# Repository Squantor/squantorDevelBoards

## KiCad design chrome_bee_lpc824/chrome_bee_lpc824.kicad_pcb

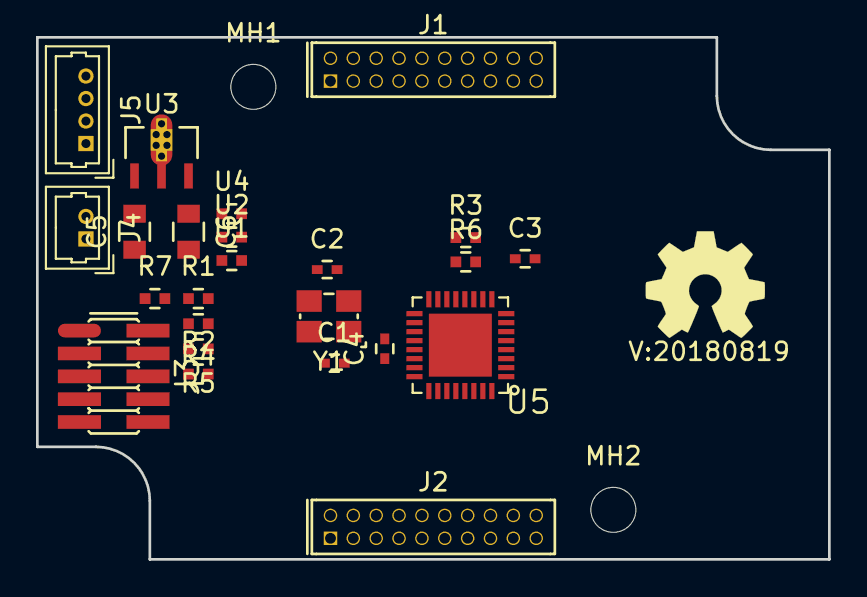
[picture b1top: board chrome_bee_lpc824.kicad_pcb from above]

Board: 4 copper layers, 44.0 x 29.0 mm, 28 parts (0 on the bottom side), 39 nets, no tracks yet.

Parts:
C1, C2: 10p; C_0402
C3, C4: 100n; C_0402
C5: 1mu; C_0805
C6: 10mu; C_0805
J1: DevBoardDigital; Header-0127-2X10-H006
J2: DevBoardAnalog; Header-0127-2X10-H006
J3: JTAG_2X05; Header-0127-2X05-SMD
J4: POWER_IN; Molex_PicoBlade_53047-0210_02x1.25mm_Straight
J5: BMP_UART; Molex_PicoBlade_53047-0410_04x1.25mm_Straight
MH1, MH2: MountingHole; MountingHole_2.5mm_no_metal
N1: OHWLOGO; OSHW-Symbol_6.7x6mm_SilkScreen
N2: 20180819; Label_version
R1, R2, R3: 100k; R_0402_hand
R4, R5, R6: 100; R_0402_hand
R7: 10; R_0402_hand
U1, U2, U4: POWER_JOINER; R_0402_hand
U3: MCP1702-MB; SOT89-ViaTab-Microchip-MB
U5: LPC824M201JHI33; SOT617-3
Y1: 12MHz; Crystal_3225_4

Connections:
/ANALOG0: J2.11, U5.22
/ANALOG1: J2.12, U5.23
/ANALOG2: J2.13, U5.25
/ANALOG3: J2.14, U5.26
/ANALOG4: J2.15, U5.27
/ANALOG5: J2.16, U5.28
/ANALOG6: J2.17, U5.29
/ANALOG7: J2.18, U5.30
/ANALOG8: J2.19, U5.31
/ANALOG9: J2.20, U5.32
/IO00_SDA: J1.5, U5.8
/IO01_SCL: J1.6, U5.9
/IO02_MOSI: J1.7, U5.2
/IO03_MISO: J1.8, U5.1
/IO04_SCK: J1.9, U5.15
/IO05_RXI: J1.10, J5.2, U5.10
/IO06_TXO: J1.11, J5.3, U5.14
/IO07: J1.12, U5.13
/IO08: J1.13, U5.12
/IO09: J1.14, U5.11
/IO10: J1.15, U5.5
/IO11: J1.16, U5.24
/IO12: J1.17, U5.16
/IO13: J1.18, U5.4
/RESET: R3.2, R6.1, U5.3
/SWDCLK: R2.2, R5.1, U5.6
/SWDIO: R1.2, R4.1, U5.7
/XTAL_IN: C1.1, U5.18, Y1.1
/XTAL_OUT: C2.1, U5.17, Y1.3
GND: C5.2, C6.2, J4.2, U1.1, U2.1, U3.1
unnamed: J3.1, R7.1
unnamed: J3.2, R4.2
unnamed: J3.4, R5.2
unnamed: J3.10, R6.2
VCC: C5.1, J2.1, J2.2, J4.1, J5.1, U3.2, U3.TAB
VDD: C3.1, C6.1, J1.1, J1.2, R1.1, R3.1, R7.2, U3.3, U4.1, U5.19
VDDA: C4.1, J2.5, J2.6, U4.2, U5.21
VSS: C1.2, C2.2, C3.2, J1.3, J1.4, J2.3, J2.4, J3.3, J3.5, J3.9, J5.4, R2.1, U1.2, U5.33, Y1.2, Y1.4
VSSA: C4.2, J2.7, J2.8, U2.2, U5.20

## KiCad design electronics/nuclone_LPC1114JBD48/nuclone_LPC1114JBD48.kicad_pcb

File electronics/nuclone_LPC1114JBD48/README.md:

# Nuclone development board for the LPC1114JBD48
Development board for the LPC1114 in TQFP48 package, actually any LPC111X series in the TQFP48 package can be mounted but the LPC1114 is mostly used.
# HSI (Hardware Software Interface)
* PIO0_0 is the reset pin but there is a default open jumper to a header pin
* PIO0_10 is the SWCLK/TCK pin but there is a default open jumper to a header pin
* PIO1_3 is the SWDIO/TMS pin but there is a default open jumper to a header pin
* The on board crystal is 12MHz in 3225 package.
## TODO's
Still some things need to be done:
* Produce at [JLCPCB](https://jlcpcb.com/)
* Assemble
* Test & characterise
* update Readme.md with pictures and BOM
## BOM
* [LPC1114FBD48/302,1](https://lcsc.com/product-detail/NXP-MCU_NXP_LPC1114FBD48-302_LPC1114FBD48-302_C9872.html)

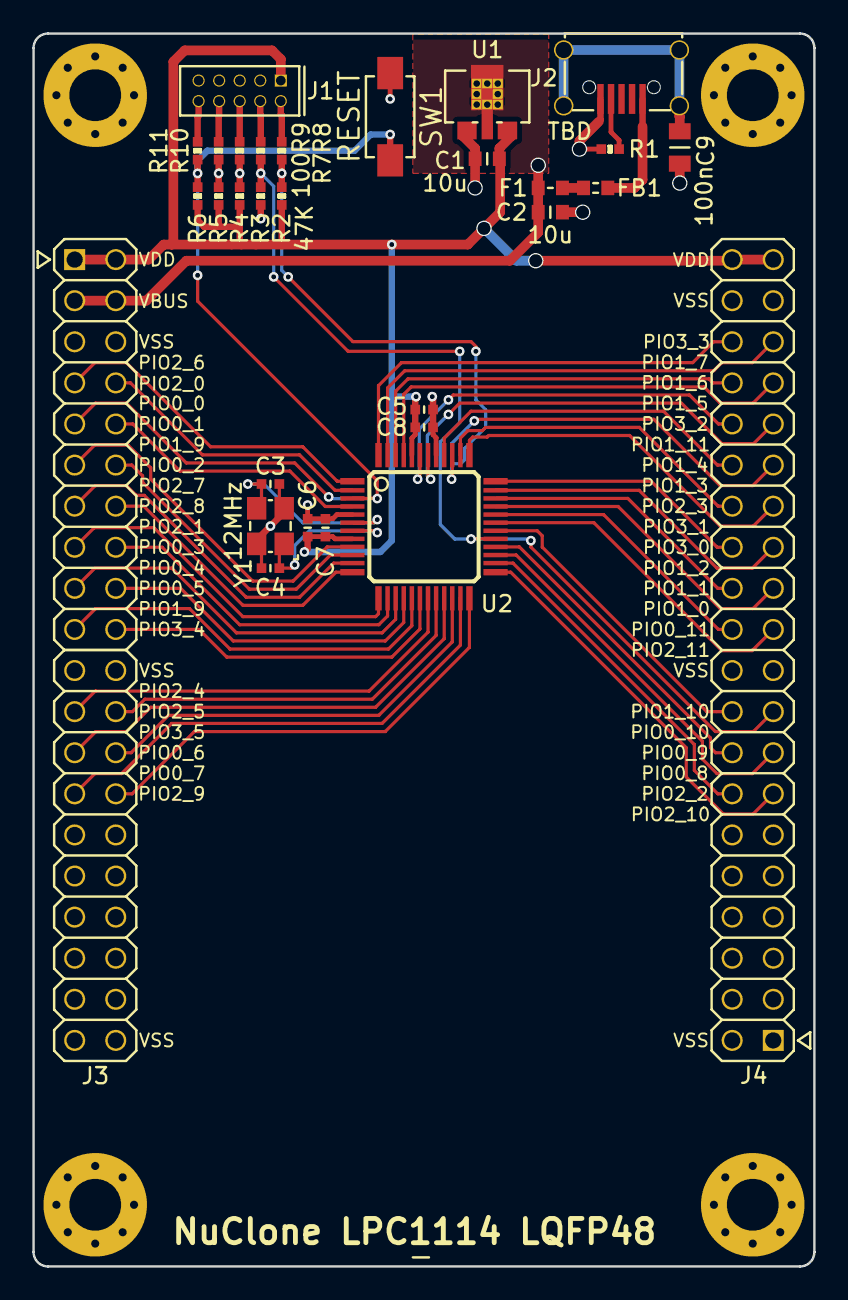
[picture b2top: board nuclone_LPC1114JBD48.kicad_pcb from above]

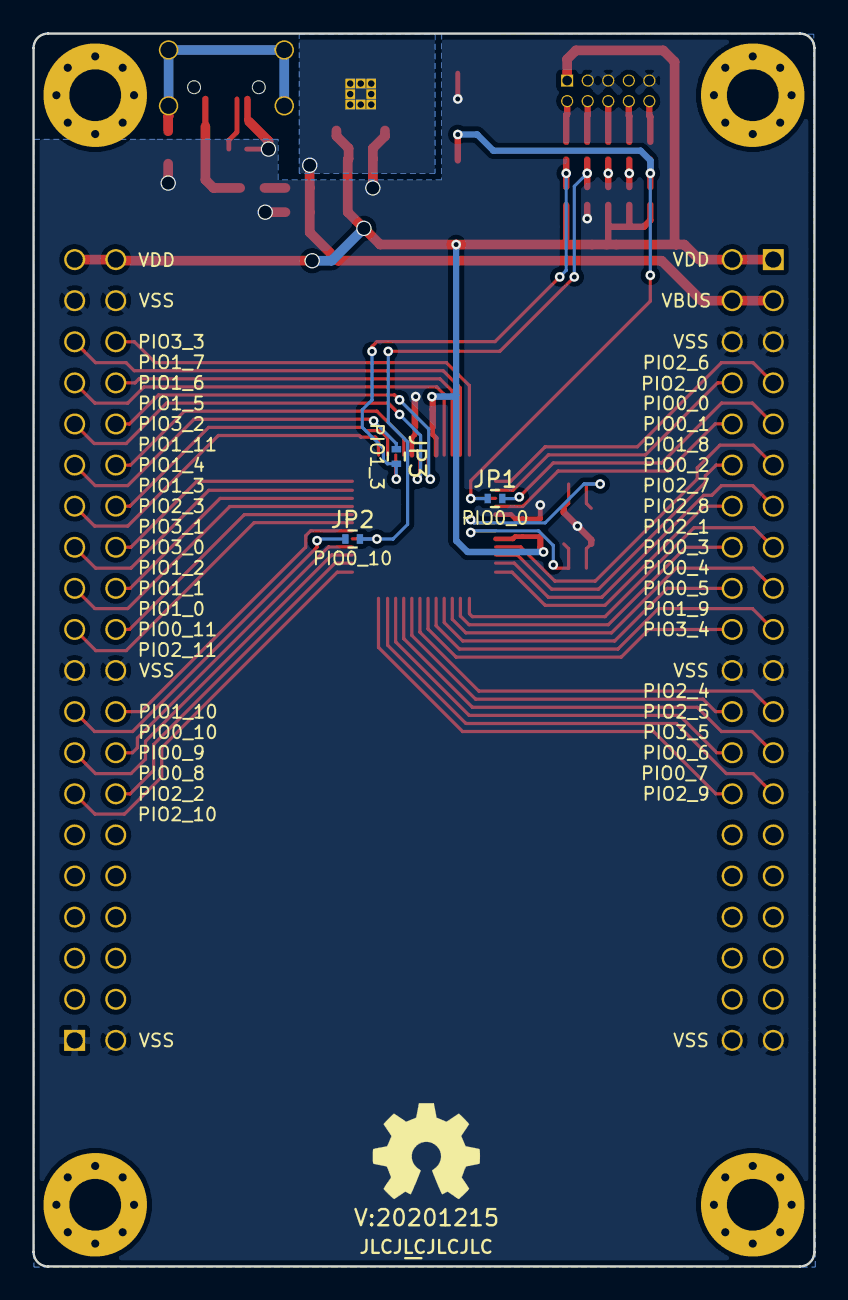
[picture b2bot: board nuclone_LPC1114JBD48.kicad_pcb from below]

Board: 2 copper layers, 48.3 x 76.2 mm, 41 parts (6 on the bottom side), 61 nets.

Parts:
C1, C2: 10u; C_0603
C3, C4: 12p; C_0402
C5, C6: 1u; C_0402
C7, C8: 100n; C_0402
C9: 100n; C_0805
F1: 0.5A; F_0603_hand
FB1: 100; L_0603
H1, H2, H3, H4: MountingHole; MountingHole_3.2mm_M3_Pad_Via
J1: JTAG_2X05; Header-0127-2X05-H006
J2: USB-ID; USB-muB-SMD_TH
J3: nuclone_small_left; nuclone_medium_left
J4: nuclone_small_right; nuclone_medium_right
JP1: PIO0_0; solder_jumper_2way_noconn
JP2: PIO0_10; solder_jumper_2way_noconn
JP3: PIO1_3; solder_jumper_2way_noconn
N1: OHWLOGO; OSHW-Symbol_6.7x6mm_SilkScreen
N2: 20201215; Label_version
N3: JLCJLCJLCJLC; Label_Generic
N4: NuClone LPC1114 LQFP48; Label_Generic
R1: TBD; R_0402_hand
R2, R3, R4, R5, R6: 47K; R_0402_hand
R7, R8, R9, R10, R11: 100; R_0402_hand
SW1: RESET; DTSM3
U1: MCP1702-MB; SOT89-SOT23-Dual-NXP
U2: LPC1114FBD48_302; SOT313-2-NXP
Y1: 12MHz; Crystal_3225_4

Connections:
/PIO0_0: J3.9 (GPIO_02), JP1.1
/PIO0_1: J3.10 (GPIO_03), U2.4 (PIO0_1/CLKOUT/CT32B0_MAT2)
/PIO0_2: J3.12 (GPIO_05), U2.10 (PIO0_2/SSEL0/CT16B0_CAP0)
/PIO0_3: J3.16 (GPIO_09), U2.14 (PIO0_3)
/PIO0_4: J3.17 (GPIO_10), U2.15 (PIO0_4/SCL)
/PIO0_5: J3.18 (GPIO_11), U2.16 (PIO0_5/SDA)
/PIO0_6: J3.26 (GPIO_17), U2.22 (PIO0_6/SCK0)
/PIO0_7: J3.27 (GPIO_18), U2.23 (PIO0_7/CTS)
/PIO0_8: J4.26 (GPIO_50), U2.27 (PIO0_8/MISO0/CT16B0_MAT0)
/PIO0_9: J4.25 (GPIO_51), U2.28 (PIO0_9/MOSI0/CT16B0_MAT1)
/PIO0_10: J4.24 (GPIO_48), JP2.1
/PIO0_11: J4.19 (VSS), U2.32 (R/PIO0_11/AD0/CT32B0_MAT3)
/PIO1_0: J4.18 (GPIO_44), U2.33 (R/PIO1_0/AD1/CT32B1_CAP0)
/PIO1_1: J4.17 (GPIO_45), U2.34 (R/PIO1_1/AD2/CT32B1_MAT0)
/PIO1_2: J4.16 (GPIO_42), U2.35 (R/PIO1_2/AD3/CT32B1_MAT1)
/PIO1_3: J4.12 (GPIO_38), JP3.1
/PIO1_4: J4.11 (GPIO_39), U2.40 (PIO1_4/AD5/CT32B1_MAT3/WAKEUP)
/PIO1_5: J4.8 (GPIO_34), U2.45 (PIO1_5/RTS/CT32B0_CAP0)
/PIO1_6: J4.7 (GPIO_35), U2.46 (PIO1_6/RXD/CT32B0_MAT0)
/PIO1_7: J4.6 (GPIO_32), U2.47 (PIO1_7/TXD/CT32B0_MAT1)
/PIO1_8: J3.11 (GPIO_04), U2.9 (PIO1_8/CT16B1_CAP0)
/PIO1_9: J3.19 (GPIO_12), U2.17 (PIO1_9/CT16B1_MAT0)
/PIO1_10: J4.23 (GPIO_49), U2.30 (PIO1_10/AD6/CT16B1_MAT1)
/PIO1_11: J4.10 (GPIO_36), U2.42 (PIO1_11/AD7)
/PIO2_0: J3.8 (GPIO_01), U2.2 (PIO2_0/DTR/SSEL1)
/PIO2_1: J3.15 (GPIO_08), U2.13 (PIO2_1/DSR/SCK1)
/PIO2_2: J4.27 (GPIO_53), U2.26 (PIO2_2/DCD/MISO1)
/PIO2_3: J4.13 (GPIO_41), U2.38 (PIO2_3/RI/MOSI1)
/PIO2_4: J3.23 (GPIO_14), U2.19 (PIO2_4)
/PIO2_5: J3.24 (GPIO_15), U2.20 (PIO2_5)
/PIO2_6: J3.7 (GPIO_00), U2.1 (PIO2_6)
/PIO2_7: J3.13 (GPIO_06), U2.11 (PIO2_7)
/PIO2_8: J3.14 (GPIO_07), U2.12 (PIO2_8)
/PIO2_9: J3.28 (GPIO_19), U2.24 (PIO2_9)
/PIO2_10: J4.28 (GPIO_52), U2.25 (PIO2_10)
/PIO2_11: J4.20 (VSS), U2.31 (PIO2_11/SCK0)
/PIO3_0: J4.15 (GPIO_43), U2.36 (PIO3_0/DTR)
/PIO3_1: J4.14 (GPIO_40), U2.37 (PIO3_1/DSR)
/PIO3_2: J4.9 (GPIO_37), U2.43 (PIO3_2/DCD)
/PIO3_3: J4.5 (GPIO_33), U2.48 (PIO3_3/RI)
/PIO3_4: J3.20 (GPIO_13), U2.18 (PIO3_4)
/PIO3_5: J3.25 (GPIO_16), U2.21 (PIO3_5)
/RESET: JP1.2, R6.1, R11.2, SW1.2, U2.3 (RESET/PIO0_0)
/TCK: JP2.2, R3.1, R8.2, U2.29 (SWCLK/PIO0_10/SCK0/CT16B0_MAT2)
/TDI: R5.1, R10.2
/TDO: R4.1, R9.2
/TMS: JP3.2, R2.1, R7.2, U2.39 (SWDIO/PIO1_3/AD4/CT32B1_MAT2)
/VBUS: C2.2, F1.1, J3.3 (VBUS), J3.4 (VBUS), U1.2 (Vin)
/VDD: C1.1, C5.1, C6.1, C7.1, C8.1, J1.1 (VCC), J3.1 (VDD), J3.2 (VDD), J4.1 (VSS), J4.2 (VSS), R2.2, R4.2, R5.2, R6.2, U1.3 (Vout), U2.8 (VDD), U2.44 (VDD)
/VSS: C1.2, C2.1, C3.2, C4.2, C5.2, C6.2, C7.2, C8.2, C9.1, J1.3 (GND), J1.5 (GND), J1.9 (GNDDET), J2.5 (GND), J3.5 (VSS), J3.6 (VSS), J3.21 (VSS), J3.22 (VSS), J3.39 (VSS), J3.40 (VSS), J4.3 (GPIO_31), J4.4 (GPIO_30), J4.21 (GPIO_47), J4.22 (GPIO_46), J4.39 (VDD), J4.40 (VDD), R1.1, R3.2, SW1.1, U1.1 (GND), U2.5 (VSS), U2.41 (VSS), Y1.2, Y1.4
unnamed: C3.1, U2.6 (XTALIN), Y1.3
unnamed: C4.1, U2.7 (XTALOUT), Y1.1
unnamed: C9.2, J2.S (Shield)
unnamed: F1.2, FB1.1
unnamed: J1.2 (SWDIO/TMS), R7.1
unnamed: J1.4 (SWDCLK/TCK), R8.1
unnamed: J1.6 (SWO/TDO), R9.1
unnamed: J1.8 (TDI), R10.1
unnamed: J1.10 (nRESET), R11.1
unnamed: FB1.2, J2.1 (VBUS)
unnamed: J2.4 (ID), R1.2

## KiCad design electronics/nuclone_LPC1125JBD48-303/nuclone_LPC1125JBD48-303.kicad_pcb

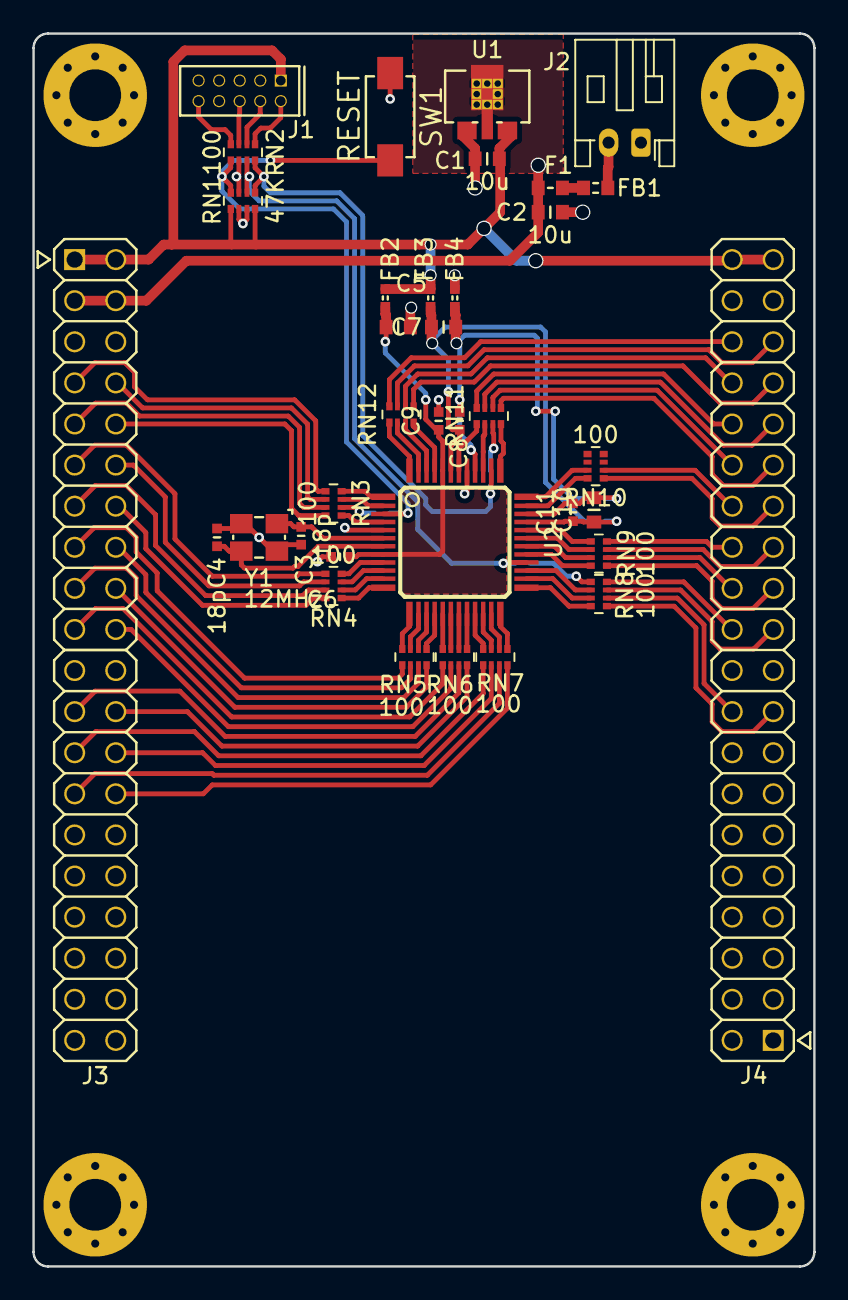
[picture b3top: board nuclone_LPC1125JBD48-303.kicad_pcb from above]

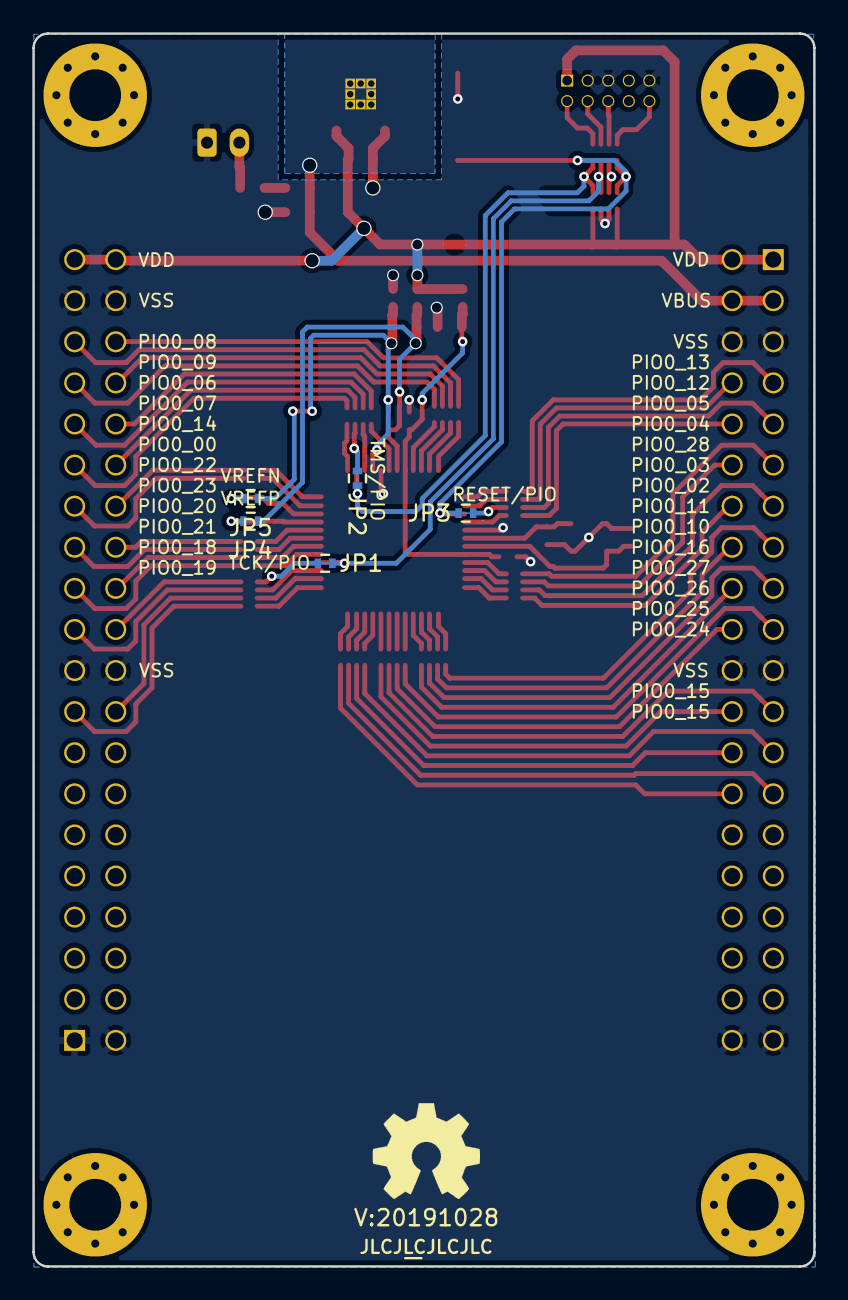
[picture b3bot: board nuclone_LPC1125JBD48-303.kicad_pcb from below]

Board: 2 copper layers, 48.3 x 76.2 mm, 48 parts (8 on the bottom side), 96 nets.

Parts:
C1, C2, C5, C7, C10: 10u; C_0603
C3, C4: 18p; C_0402
C6, C8, C9, C11: 1u; C_0402
F1: 0.5A; F_0603_hand
FB1: 100; L_0603
FB2, FB3, FB4: FB; L_0402
H1, H2, H3, H4: MountingHole; MountingHole_3.2mm_M3_Pad_Via
J1: JTAG_2X05; Header-0127-2X05-H006
J2: Conn_01x02; JST_PH_S2B-PH-K_1x02_P2.00mm_Horizontal
J3: nuclone_small_left; nuclone_medium_left
J4: nuclone_small_right; nuclone_medium_right
JP1: TCK/PIO; solder_jumper_2way_conn
JP2: TMS/PIO; solder_jumper_2way_conn
JP3: RESET/PIO; solder_jumper_2way_conn
JP4: VREFP; solder_jumper_2way_conn
JP5: VREFN; solder_jumper_2way_conn
N1: OHWLOGO; OSHW-Symbol_6.7x6mm_SilkScreen
N2: 20191028; Label_version
N3: JLCJLCJLCJLC; Label_Generic
RN1: 47K; R_Array_Convex_4x0402
RN2, RN3, RN4, RN5, RN6, RN7, RN8, RN9, RN10, RN11, RN12: 100; R_Array_Convex_4x0402
SW1: RESET; DTSM3
U1: MCP1702-MB; SOT89-SOT23-Dual-NXP
U2: LPC1125JBD48_303; SOT313-2-NXP
Y1: 12MHz; Crystal_3225_4

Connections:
/PIO0_0: JP3.1, RN3.2
/PIO0_0_MCU: JP3.2, RN1.8, RN2.5, SW1.2, U2.3
/PIO0_0_OUT: J3.9, RN3.7
/PIO0_1_MCU: RN3.1, U2.4
/PIO0_1_OUT: J3.10, RN3.8
/PIO0_2_MCU: RN4.3, U2.10
/PIO0_2_OUT: J3.12, RN4.6
/PIO0_3_MCU: RN5.3, U2.14
/PIO0_3_OUT: J3.16, RN5.6
/PIO0_4_MCU: RN5.2, U2.15
/PIO0_4_OUT: J3.17, RN5.7
/PIO0_5_MCU: RN5.1, U2.16
/PIO0_5_OUT: J3.18, RN5.8
/PIO0_6_MCU: RN7.3, U2.22
/PIO0_6_OUT: J3.26, RN7.6
/PIO0_7_MCU: RN7.2, U2.23
/PIO0_7_OUT: J3.27, RN7.7
/PIO0_8_MCU: RN8.3, U2.26
/PIO0_8_OUT: J4.18, RN8.6
/PIO0_9_MCU: RN8.2, U2.27
/PIO0_9_OUT: J4.21, RN8.7
/PIO0_10: JP1.1, RN8.1
/PIO0_10_MCU: JP1.2, RN1.6, RN2.7, U2.28
/PIO0_10_OUT: J4.22, RN8.8
/PIO0_11_MCU: RN9.3, U2.30
/PIO0_11_OUT: J4.24, RN9.6
/PIO1_0_MCU: RN9.2, U2.31
/PIO1_0_OUT: J4.25, RN9.7
/PIO1_1_MCU: RN9.1, U2.32
/PIO1_1_OUT: J4.26, RN9.8
/PIO1_2_MCU: RN10.4, U2.35
/PIO1_2_OUT: J4.27, RN10.5
/PIO1_3: JP2.1, RN11.3
/PIO1_3_MCU: JP2.2, RN1.5, RN2.8, U2.38
/PIO1_3_OUT: J4.30, RN11.6
/PIO1_4_MCU: RN11.2, U2.39
/PIO1_4_OUT: J4.31, RN11.7
/PIO1_5_MCU: RN12.4, U2.45
/PIO1_5_OUT: J4.33, RN12.5
/PIO1_6_MCU: RN12.3, U2.46
/PIO1_6_OUT: J4.34, RN12.6
/PIO1_7_MCU: RN12.2, U2.47
/PIO1_7_OUT: J4.35, RN12.7
/PIO1_8_MCU: RN4.4, U2.9
/PIO1_8_OUT: J3.11, RN4.5
/PIO1_9_MCU: RN6.4, U2.17
/PIO1_9_OUT: J3.19, RN6.5
/PIO1_10_MCU: RN9.4, U2.29
/PIO1_10_OUT: J4.23, RN9.5
/PIO1_11_MCU: RN11.1, U2.42
/PIO1_11_OUT: J4.32, RN11.8
/PIO2_0_MCU: RN3.3, U2.2
/PIO2_0_OUT: J3.8, RN3.6
/PIO2_1_MCU: RN5.4, U2.13
/PIO2_1_OUT: J3.15, RN5.5
/PIO2_2_MCU: RN8.4, U2.25
/PIO2_2_OUT: J4.17, RN8.5
/PIO2_3_MCU: RN11.4, U2.37
/PIO2_3_OUT: J4.29, RN11.5
/PIO2_4_MCU: RN6.2, U2.19
/PIO2_4_OUT: J3.23, RN6.7
/PIO2_5_MCU: RN6.1, U2.20
/PIO2_5_OUT: J3.24, RN6.8
/PIO2_6_MCU: RN3.4, U2.1
/PIO2_6_OUT: J3.7, RN3.5
/PIO2_7_MCU: RN4.2, U2.11
/PIO2_7_OUT: J3.13, RN4.7
/PIO2_8_MCU: RN4.1, U2.12
/PIO2_8_OUT: J3.14, RN4.8
/PIO2_9_MCU: RN7.1, U2.24
/PIO2_9_OUT: J3.28, RN7.8
/PIO3_0_MCU: RN10.3, U2.36
/PIO3_0_OUT: J4.28, RN10.6
/PIO3_3_MCU: RN12.1, U2.48
/PIO3_3_OUT: J4.36, RN12.8
/PIO3_4_MCU: RN6.3, U2.18
/PIO3_4_OUT: J3.20, RN6.6
/PIO3_5_MCU: RN7.4, U2.21
/PIO3_5_OUT: J3.25, RN7.5
/SWO_TDO: RN1.7, RN2.6
/VBUS: C2.2, F1.1, J3.3, J3.4, U1.2
/VDD: C1.1, FB2.2, FB3.2, J1.1, J3.1, J3.2, J4.39, J4.40, RN1.1, RN1.4, U1.3
/VDDA_MCU: C7.1, C8.1, FB3.1, JP4.1, U2.43
/VDD_MCU: C5.1, C6.1, C9.1, FB2.1, U2.8, U2.44
/VREFN_MCU: C10.2, C11.2, JP5.2, U2.34
/VREFP_MCU: C10.1, C11.1, JP4.2, U2.33
/VSSA_MCU: C7.2, C8.2, FB4.1, JP5.1, U2.40
/XTAL_IN: C3.1, U2.6, Y1.1
/XTAL_OUT: C4.1, U2.7, Y1.3
unnamed: F1.2, FB1.1
unnamed: FB1.2, J2.2
unnamed: J1.2, RN2.1
unnamed: J1.4, RN2.2
unnamed: J1.6, RN2.3
unnamed: J1.10, RN2.4
VSS: C1.2, C2.1, C3.2, C4.2, C5.2, C6.2, C9.2, FB4.2, J1.3, J1.5, J1.9, J2.1, J3.5, J3.6, J3.21, J3.22, J3.39, J3.40, J4.1, J4.2, J4.19, J4.20, J4.37, J4.38, RN1.2, RN1.3, SW1.1, U1.1, U2.5, U2.41, Y1.2, Y1.4

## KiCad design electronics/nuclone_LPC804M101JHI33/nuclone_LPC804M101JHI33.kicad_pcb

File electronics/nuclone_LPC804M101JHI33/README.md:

# Nuclone development board for LPC804M101JHI33
LPC804M101JHI33 development board inspired by the nucleo series from STM32.
## TODO's
Still some things need to be done:
* everything!

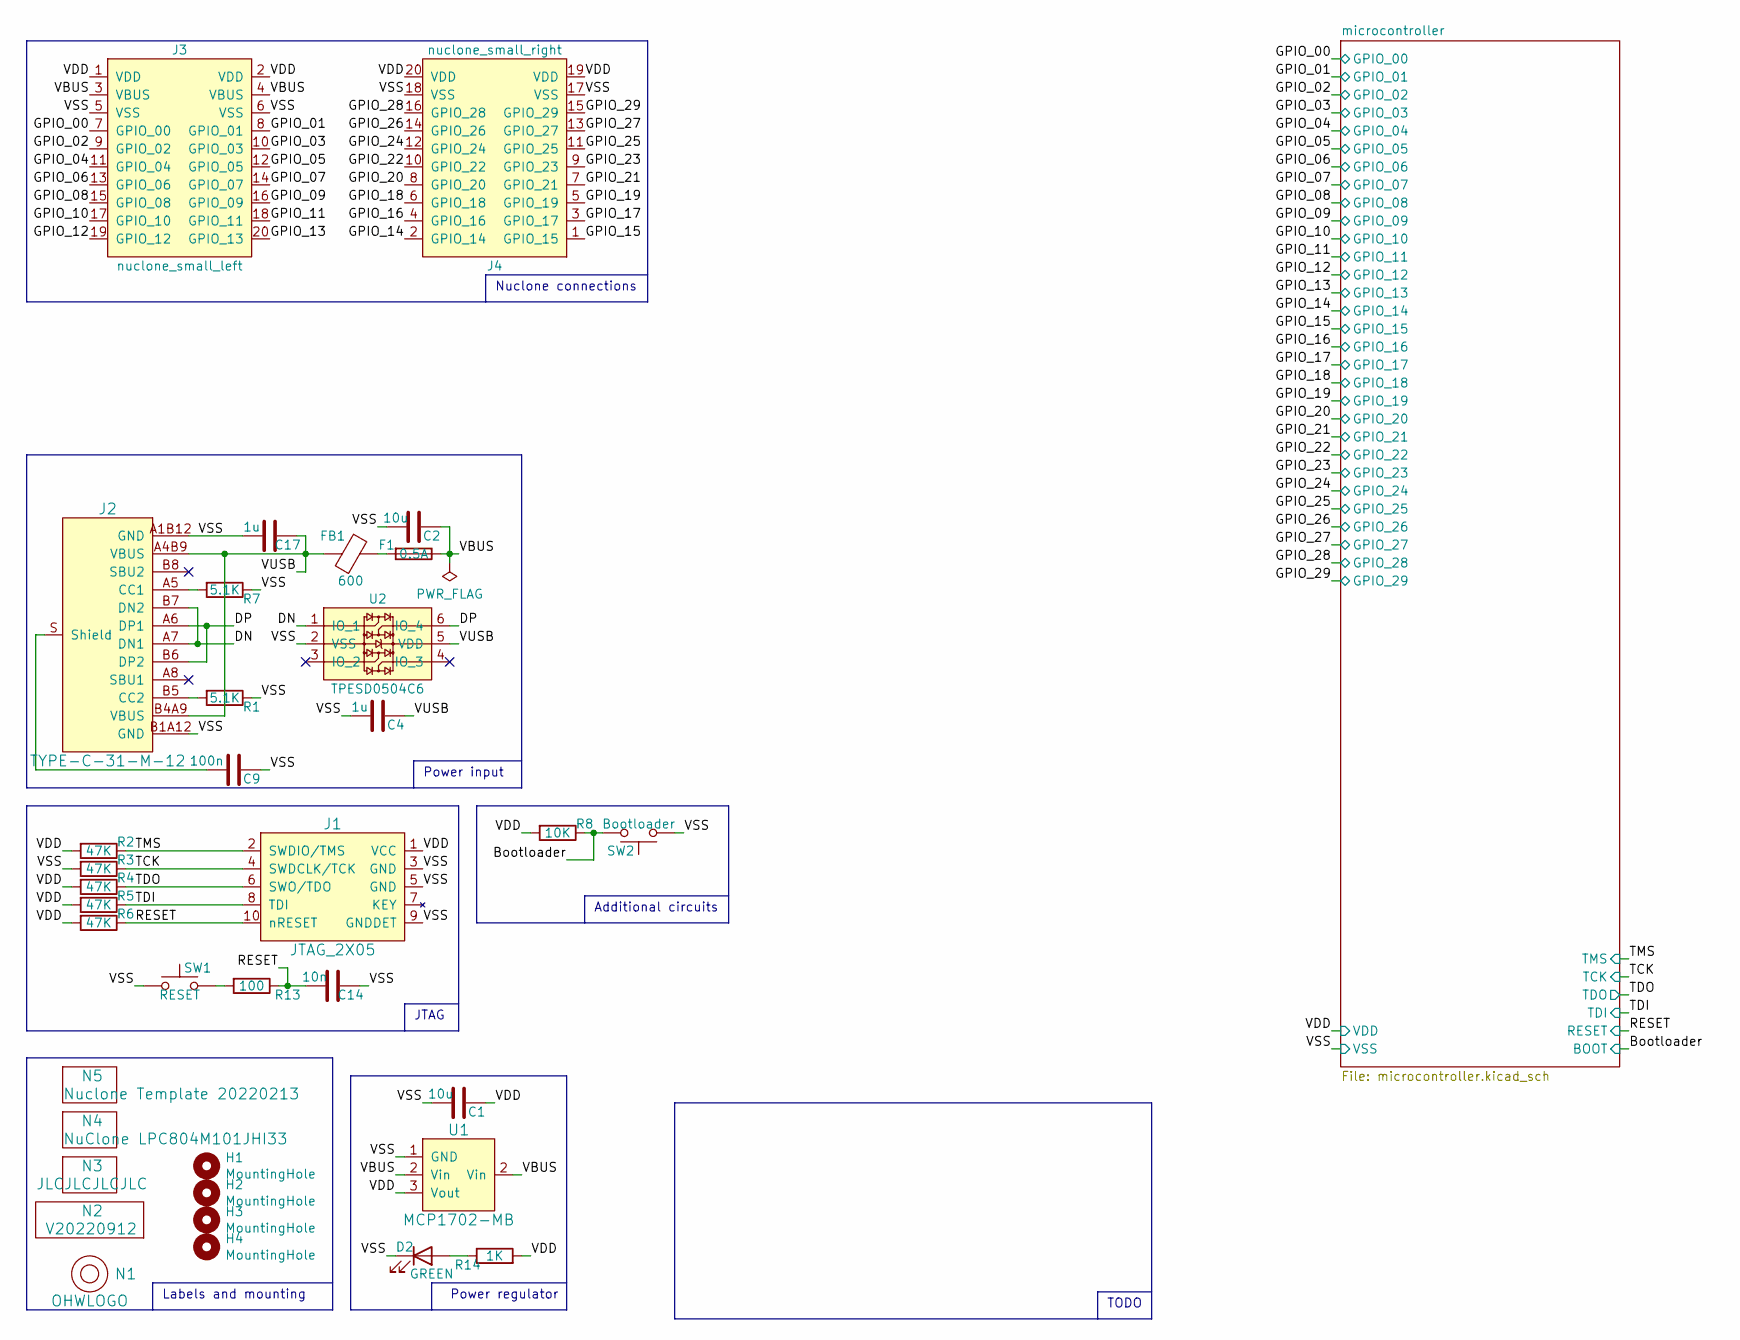
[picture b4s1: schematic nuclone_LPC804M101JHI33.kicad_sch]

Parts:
C1, C2: 10u; C_0603
C4: 1u; C_0402
C9: 100n; C_0805
C14: 10n; C_0402
C17: 1u; C_0603
D2: GREEN; LED_0603_hand
F1: 0.5A; F_0603_hand
FB1: 600; L_0603
H1, H2, H3, H4: MountingHole; MountingHole_3.2mm_M3_Pad_Via
J1: JTAG_2X05; Header-0127-2X05-H006
J2: TYPE-C-31-M-12; USB-C-HRO-31-M-12
J3: nuclone_small_left; nuclone_small_left_stacked
J4: nuclone_small_right; nuclone_small_right_stacked
N1: OHWLOGO; OSHW-Symbol_6.7x6mm_SilkScreen
N2: V20220912; Label_Generic
N3: JLCJLCJLCJLC; Label_Generic
N4: NuClone LPC804M101JHI33; Label_Generic
N5: Nuclone Template 20220213; Label_Generic
R1, R7: 5.1K; R_0402_hand
R2, R3, R4, R5, R6: 47K; R_0402_hand
R8: 10K; R_0402_hand
R13: 100; R_0402_hand
R14: 1K; R_0402_hand
SW1: RESET; TD-85XU
SW2: Bootloader; TD-85XU
U1: MCP1702-MB; SOT89-NXP
U2: TPESD0504C6; SOT363-ONsemi

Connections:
/Bootloader: R8.1, SW2.2; also elsewhere on the board
/DN: J2.A7 (DN1), J2.B7 (DN2), U2.1 (IO_1)
/DP: J2.A6 (DP1), J2.B6 (DP2), U2.6 (IO_4)
/GPIO_00: J3.7 (GPIO_00); also elsewhere on the board
/GPIO_01: J3.8 (GPIO_01); also elsewhere on the board
/GPIO_02: J3.9 (GPIO_02); also elsewhere on the board
/GPIO_03: J3.10 (GPIO_03); also elsewhere on the board
/GPIO_04: J3.11 (GPIO_04); also elsewhere on the board
/GPIO_05: J3.12 (GPIO_05); also elsewhere on the board
/GPIO_06: J3.13 (GPIO_06); also elsewhere on the board
/GPIO_07: J3.14 (GPIO_07); also elsewhere on the board
/GPIO_08: J3.15 (GPIO_08); also elsewhere on the board
/GPIO_09: J3.16 (GPIO_09); also elsewhere on the board
/GPIO_10: J3.17 (GPIO_10); also elsewhere on the board
/GPIO_11: J3.18 (GPIO_11); also elsewhere on the board
/GPIO_12: J3.19 (GPIO_12); also elsewhere on the board
/GPIO_13: J3.20 (GPIO_13); also elsewhere on the board
/GPIO_14: J4.2 (GPIO_14); also elsewhere on the board
/GPIO_15: J4.1 (GPIO_15); also elsewhere on the board
/GPIO_16: J4.4 (GPIO_16); also elsewhere on the board
/GPIO_17: J4.3 (GPIO_17); also elsewhere on the board
/GPIO_18: J4.6 (GPIO_18); also elsewhere on the board
/GPIO_19: J4.5 (GPIO_19); also elsewhere on the board
/GPIO_20: J4.8 (GPIO_20); also elsewhere on the board
/GPIO_21: J4.7 (GPIO_21); also elsewhere on the board
/GPIO_22: J4.10 (GPIO_22); also elsewhere on the board
/GPIO_23: J4.9 (GPIO_23); also elsewhere on the board
/GPIO_24: J4.12 (GPIO_24); also elsewhere on the board
/GPIO_25: J4.11 (GPIO_25); also elsewhere on the board
/GPIO_26: J4.14 (GPIO_26); also elsewhere on the board
/GPIO_27: J4.13 (GPIO_27); also elsewhere on the board
/GPIO_28: J4.16 (GPIO_28); also elsewhere on the board
/GPIO_29: J4.15 (GPIO_29); also elsewhere on the board
/RESET: C14.2, J1.10 (nRESET), R6.1, R13.1; also elsewhere on the board
/TCK: J1.4 (SWDCLK/TCK), R3.1; also elsewhere on the board
/TDI: J1.8 (TDI), R5.1
/TDO: J1.6 (SWO/TDO), R4.1
/TMS: J1.2 (SWDIO/TMS), R2.1; also elsewhere on the board
/VBUS: C2.2, F1.1, J3.3 (VBUS), J3.4 (VBUS), U1.2 (Vin)
/VDD: C1.1, J1.1 (VCC), J3.1 (VDD), J3.2 (VDD), J4.19 (VDD), J4.20 (VDD), R2.2, R4.2, R5.2, R6.2, R8.2, R14.2, U1.3 (Vout); also elsewhere on the board
/VSS: C1.2, C2.1, C4.2, C9.1, C14.1, C17.1, D2.1 (K), J1.3 (GND), J1.5 (GND), J1.9 (GNDDET), J2.A1B12 (GND), J2.B1A12 (GND), J3.5 (VSS), J3.6 (VSS), J4.17 (VSS), J4.18 (VSS), R1.1, R3.2, R7.1, SW1.1, SW2.1, U1.1 (GND), U2.2 (VSS); also elsewhere on the board
/VUSB: C4.1, C17.2, FB1.2, J2.A4B9 (VBUS), J2.B4A9 (VBUS), U2.5 (VDD)
unnamed: C9.2, J2.S (Shield)
unnamed: D2.2 (A), R14.1
unnamed: F1.2, FB1.1
unnamed: J2.A5 (CC1), R7.2
unnamed: J2.B5 (CC2), R1.2
unnamed: R13.2, SW1.2

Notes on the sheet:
Power input
Labels and mounting
Additional circuits
Nuclone connections
JTAG
TODO
Power regulator

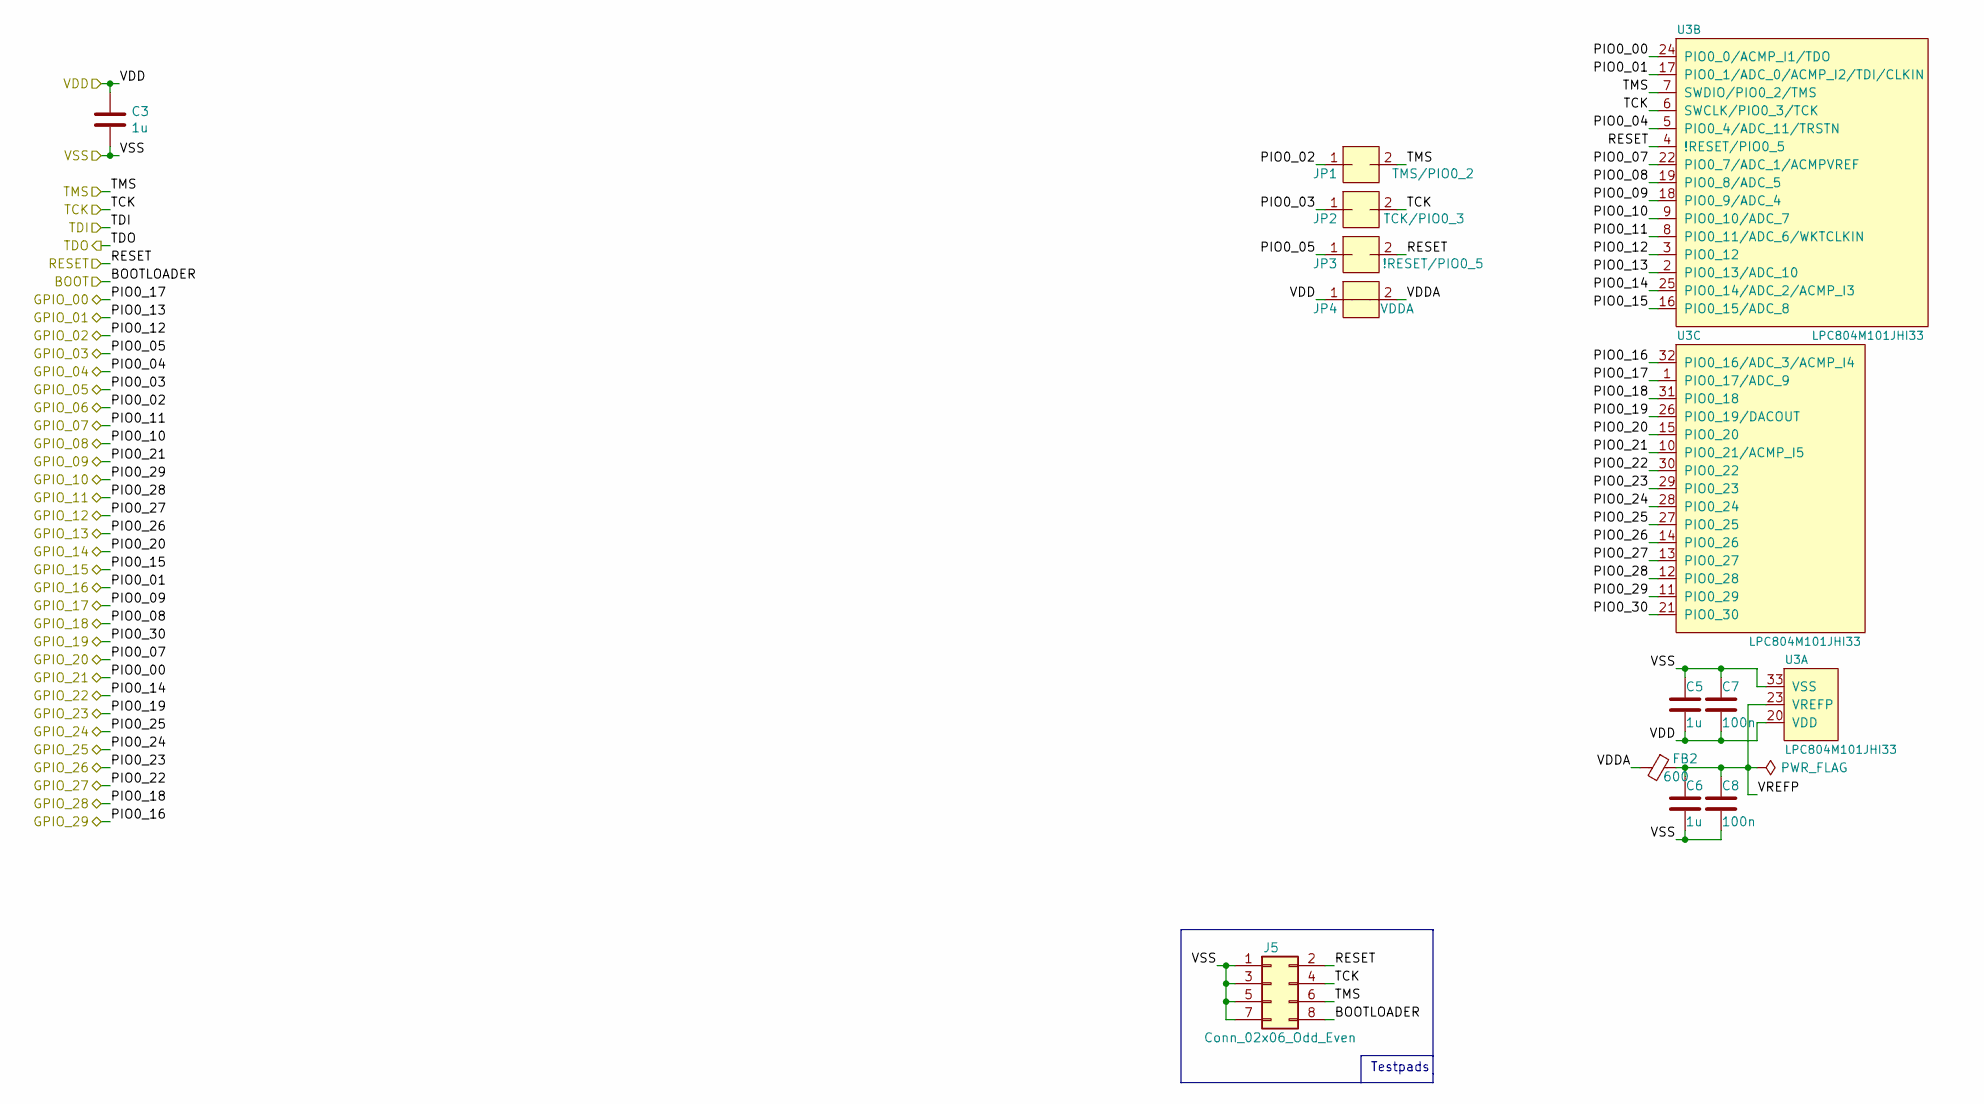
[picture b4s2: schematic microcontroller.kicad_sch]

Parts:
C3, C5, C6: 1u; C_0402
C7, C8: 100n; C_0402
FB2: 600; L_0402
J5: Conn_02x06_Odd_Even; Header-0127-2X04-H006
JP1: TMS/PIO0_2; solder_jumper_0402_2way_noconn
JP2: TCK/PIO0_3; solder_jumper_0402_2way_noconn
JP3: !RESET/PIO0_5; solder_jumper_0402_2way_noconn
JP4: VDDA; solder_jumper_0402_2way_conn
U3: LPC804M101JHI33; SOT617-3_alt_paste

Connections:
/Bootloader: J5.8; also elsewhere on the board
/GPIO_00: U3.1 (PIO0_17/ADC_9); also elsewhere on the board
/GPIO_01: U3.2 (PIO0_13/ADC_10); also elsewhere on the board
/GPIO_02: U3.3 (PIO0_12); also elsewhere on the board
/GPIO_03: JP3.1; also elsewhere on the board
/GPIO_04: U3.5 (PIO0_4/ADC_11/TRSTN); also elsewhere on the board
/GPIO_05: JP2.1; also elsewhere on the board
/GPIO_06: JP1.1; also elsewhere on the board
/GPIO_07: U3.8 (PIO0_11/ADC_6/WKTCLKIN); also elsewhere on the board
/GPIO_08: U3.9 (PIO0_10/ADC_7); also elsewhere on the board
/GPIO_09: U3.10 (PIO0_21/ACMP_I5); also elsewhere on the board
/GPIO_10: U3.11 (PIO0_29); also elsewhere on the board
/GPIO_11: U3.12 (PIO0_28); also elsewhere on the board
/GPIO_12: U3.13 (PIO0_27); also elsewhere on the board
/GPIO_13: U3.14 (PIO0_26); also elsewhere on the board
/GPIO_14: U3.15 (PIO0_20); also elsewhere on the board
/GPIO_15: U3.16 (PIO0_15/ADC_8); also elsewhere on the board
/GPIO_16: U3.17 (PIO0_1/ADC_0/ACMP_I2/TDI/CLKIN); also elsewhere on the board
/GPIO_17: U3.18 (PIO0_9/ADC_4); also elsewhere on the board
/GPIO_18: U3.19 (PIO0_8/ADC_5); also elsewhere on the board
/GPIO_19: U3.21 (PIO0_30); also elsewhere on the board
/GPIO_20: U3.22 (PIO0_7/ADC_1/ACMPVREF); also elsewhere on the board
/GPIO_21: U3.24 (PIO0_0/ACMP_I1/TDO); also elsewhere on the board
/GPIO_22: U3.25 (PIO0_14/ADC_2/ACMP_I3); also elsewhere on the board
/GPIO_23: U3.26 (PIO0_19/DACOUT); also elsewhere on the board
/GPIO_24: U3.27 (PIO0_25); also elsewhere on the board
/GPIO_25: U3.28 (PIO0_24); also elsewhere on the board
/GPIO_26: U3.29 (PIO0_23); also elsewhere on the board
/GPIO_27: U3.30 (PIO0_22); also elsewhere on the board
/GPIO_28: U3.31 (PIO0_18); also elsewhere on the board
/GPIO_29: U3.32 (PIO0_16/ADC_3/ACMP_I4); also elsewhere on the board
/RESET: J5.2, JP3.2, U3.4 (!RESET/PIO0_5); also elsewhere on the board
/TCK: J5.4, JP2.2, U3.6 (SWCLK/PIO0_3/TCK); also elsewhere on the board
/TMS: J5.6, JP1.2, U3.7 (SWDIO/PIO0_2/TMS); also elsewhere on the board
/VDD: C3.1, C5.2, C7.2, JP4.1, U3.20 (VDD); also elsewhere on the board
/VSS: C3.2, C5.1, C6.2, C7.1, C8.2, J5.1, J5.3, J5.5, J5.7, U3.33 (VSS); also elsewhere on the board
/microcontroller/VDDA: FB2.2, JP4.2
/microcontroller/VREFP: C6.1, C8.1, FB2.1, U3.23 (VREFP)

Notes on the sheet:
Testpads

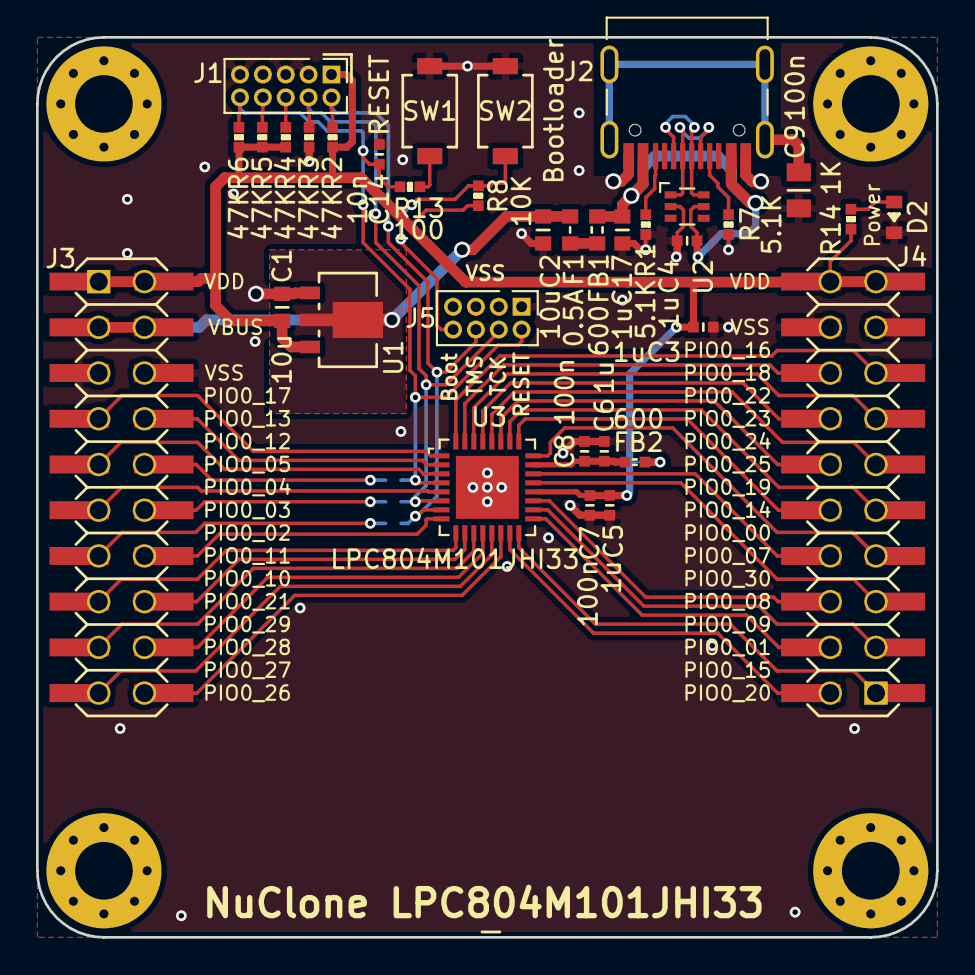
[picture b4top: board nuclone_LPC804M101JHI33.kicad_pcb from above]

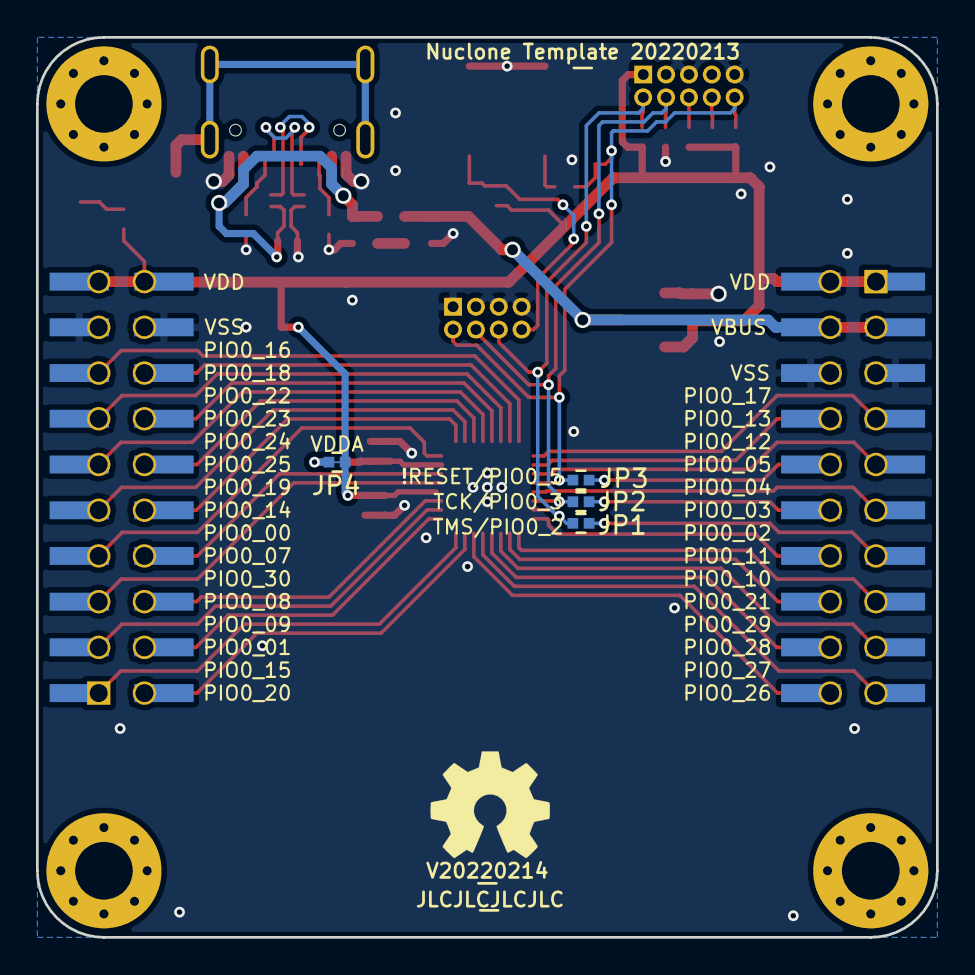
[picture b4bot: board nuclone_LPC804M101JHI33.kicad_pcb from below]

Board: 2 copper layers, 50.0 x 50.0 mm, 48 parts (8 on the bottom side), 50 nets.
